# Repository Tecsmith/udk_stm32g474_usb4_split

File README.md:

# UDK Module - STM32F474 *(with 4-Port hub)*

**Keyboard MCU**

- *Refer to https://github.com/tecsmith/udk for information on the **Universal Design Keyboards** (UDK) - MCU Modules*

# Featuring

- `STM32G474`
- `CH334` (3-ports exposed as USB-A receptacles)

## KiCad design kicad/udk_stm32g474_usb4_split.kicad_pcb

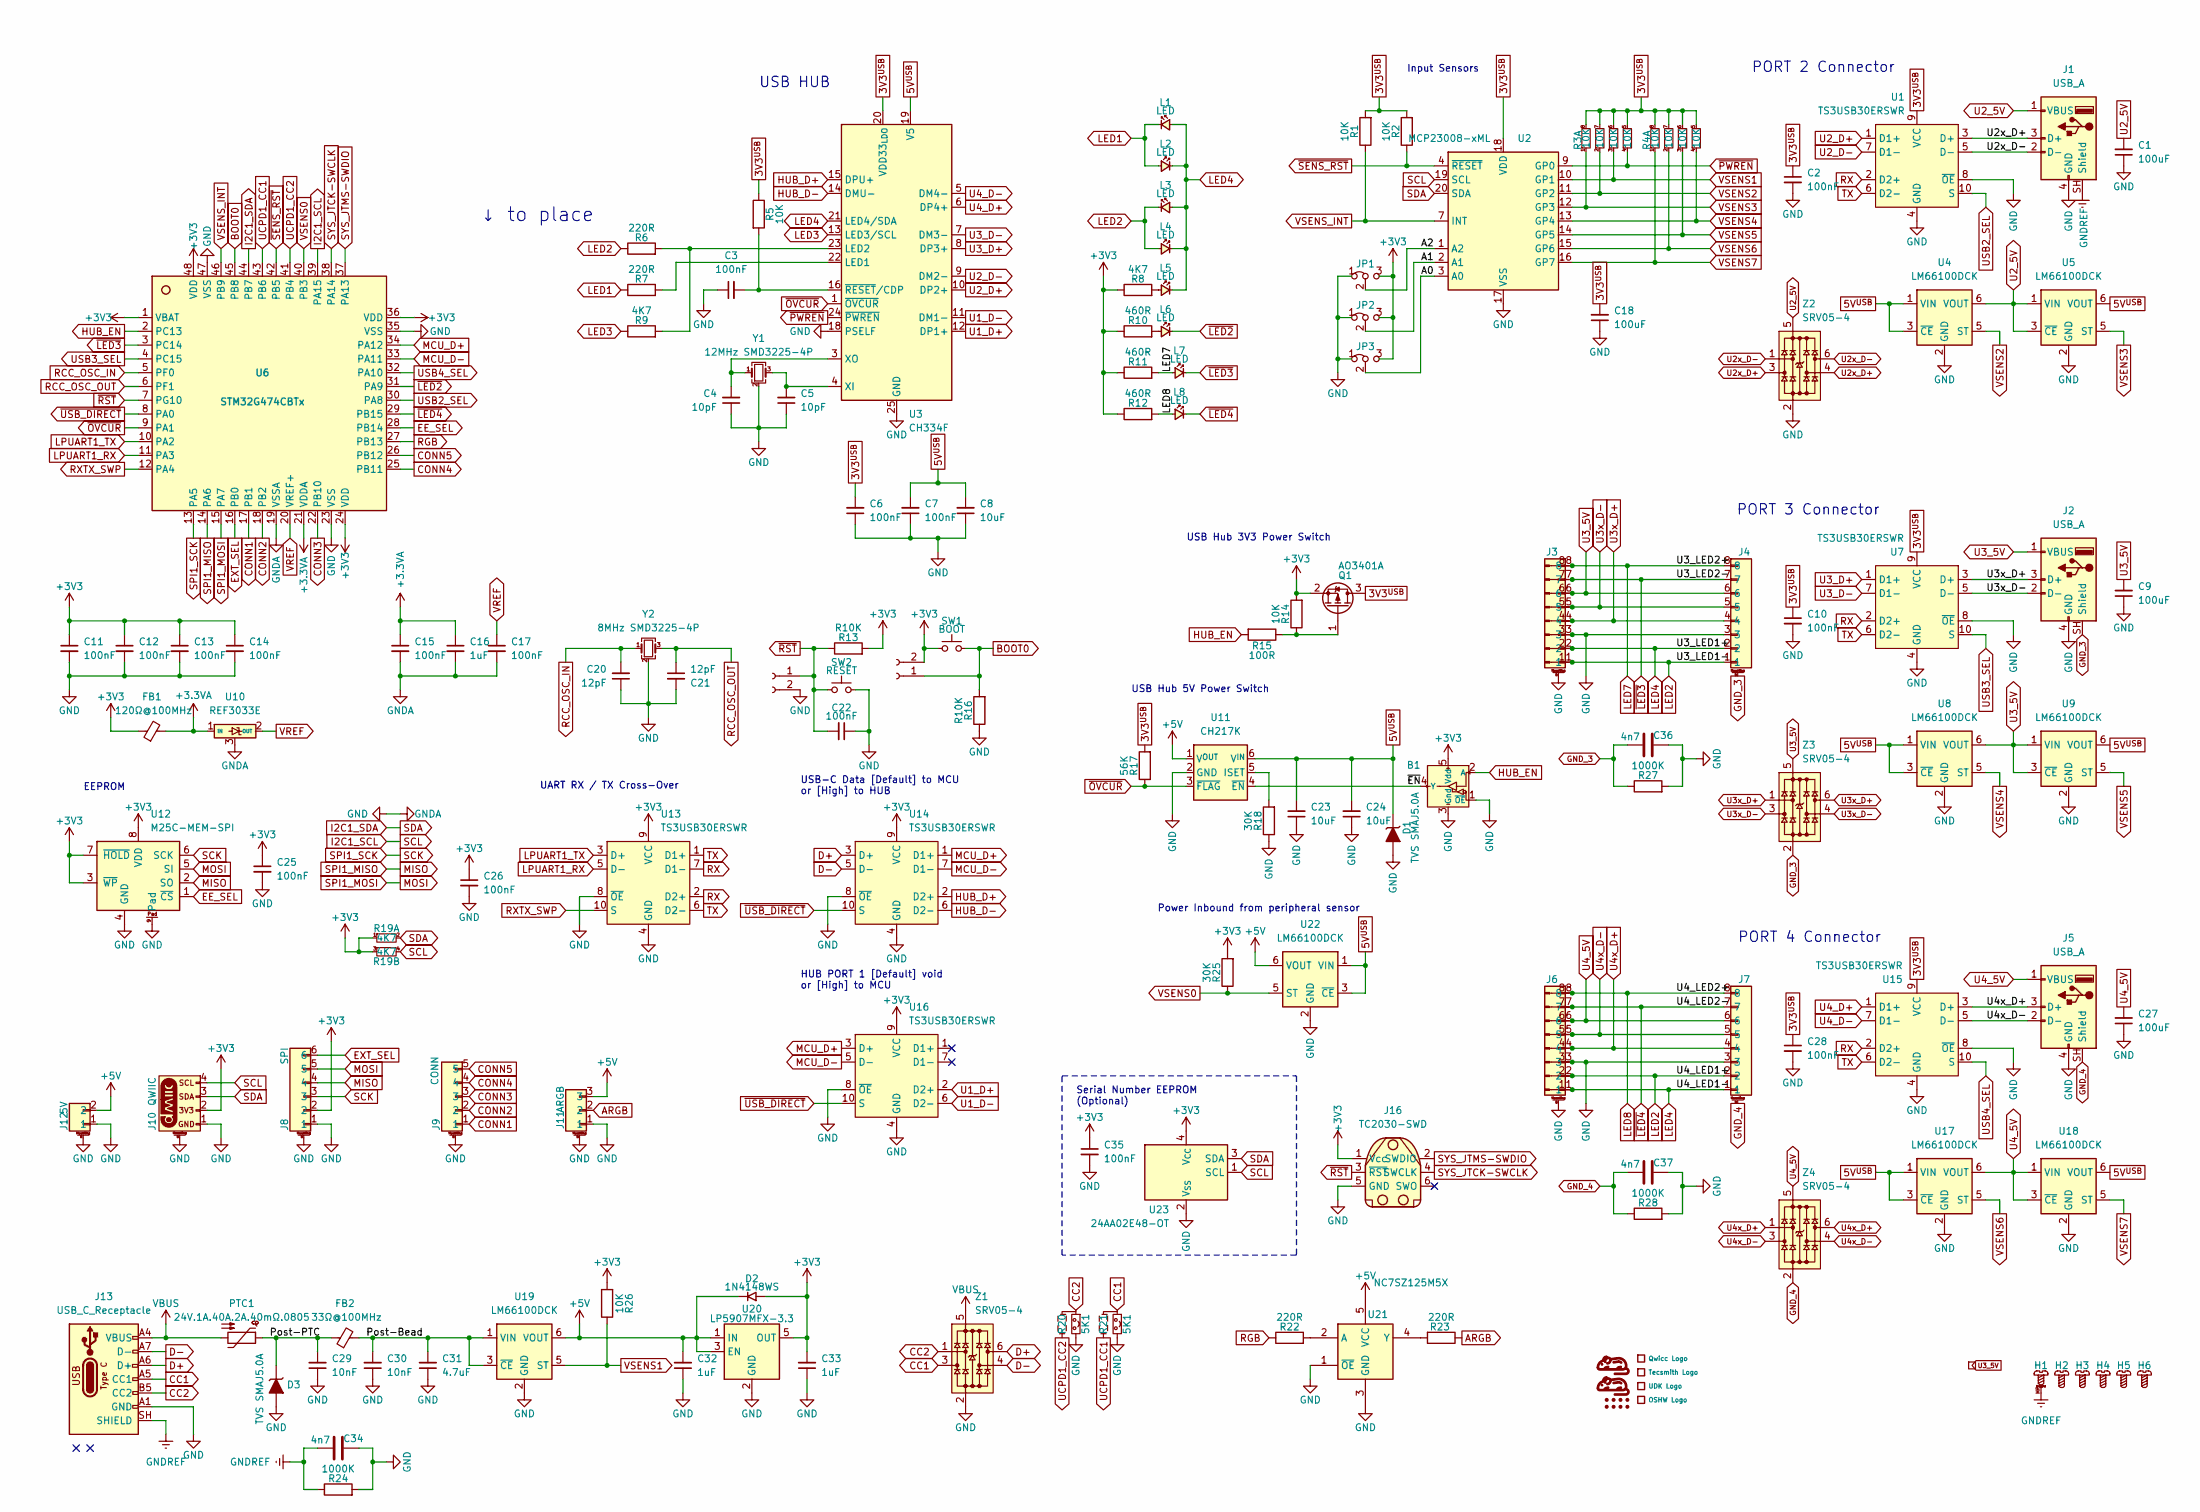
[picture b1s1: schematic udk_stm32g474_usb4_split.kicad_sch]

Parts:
B1: SOT-23-5
B2, B3: mouse-bite-2mm-slot
C1, C9, C27: 100uF; C_0603_1608Metric
C2, C3, C6, C10, C11, C12, C13, C14, C15, C17, C22, C25, C26, C28, C35: 100nF; C_0402_1005Metric
C4, C5: 10pF; C_0402_1005Metric
C7: 100nF; C_0603_1608Metric
C8, C23, C24: 10uF; C_0603_1608Metric
C16: 1uF; C_0402_1005Metric
C18: 100uF; C_0402_1005Metric
C20, C21: 12pF; C_0402_1005Metric
C29, C30: 10nF; C_0603_1608Metric
C31: 4.7uF; C_0603_1608Metric
C32, C33: 1uF; C_0603_1608Metric
C34, C36, C37: 4n7; C_0805_2012Metric_Pad1.18x1.45mm_HandSolder
D1, D3: TVS SMAJ5.0A; D_SMA
D2: 1N4148WS; D_SOD-323_HandSoldering
FB1: 120Ω@100MHz; L_0603_1608Metric; LCSC C88984
FB2: 33Ω@100MHz; L_0603_1608Metric; LCSC C88984
H1: Mount_M2_Rel
H2, H3, H4, H5, H6: Hole_M2
J1, J2, J5: USB_A; USB_A_Molex_67643_Horizontal
J3, J4, J6, J7: JST_SH_SM08B-SRSS-TB_1x08-1MP_P1.00mm_Horizontal
J8: SPI; JST_SH_SM06B-SRSS-TB_1x06-1MP_P1.00mm_Horizontal
J9: CONN; JST_SH_SM05B-SRSS-TB_1x05-1MP_P1.00mm_Horizontal
J10: QWIIC; JST_SH_SM04B-SRSS-TB_1x04-1MP_P1.00mm_Horizontal
J11: ARGB; JST_SH_SM03B-SRSS-TB_1x03-1MP_P1.00mm_Horizontal
J12: 5V; JST_SH_SM02B-SRSS-TB_1x02-1MP_P1.00mm_Horizontal
J13: USB_C_Receptacle; USB_C_Receptacle_GCT_USB4105-xx-A_16P_TopMnt_Horizontal
J14, J15: Conn_01x08_Pin; mouse-bite-2mm-weave
J16: TC2030-SWD; Tag-Connect_TC2030-IDC-NL_2x03_P1.27mm_Vertical
J17, J18: Conn_01x02_Socket; PinSocket_1x02_P2.54mm_Vertical
JP1, JP2, JP3: Jumper_3_Bridged12; SolderJumper-3_P1.3mm_Bridged12_RoundedPad1.0x1.5mm
L1, L2, L3, L4, L5, L6, L7, L8: LED; LED_0603_1608Metric
PTC1: 24V.1A.40A.2A.40mΩ.0805; L_0805_2012Metric; LCSC C42369218
Q1: AO3401A; SOT-23
R1, R2, R5, R14, R26: 10K; R_0402_1005Metric
R3, R4: 10K; R_Array_Convex_4x0402
R6, R7: 220R; R_0402_1005Metric
R8, R9: 4K7; R_0402_1005Metric
R10, R11, R12: 460R; R_0402_1005Metric
R13, R16: R10K; R_0402_1005Metric
R15: 100R; R_0402_1005Metric
R17: 56K; R_0402_1005Metric
R18, R25: 30K; R_0402_1005Metric
R19: 4K7; R_0603_1608_2up
R20: 5K1; Jumper_R_0603_M
R21: 5K1; Jumper_R_0603
R22, R23: 220R; R_0603_1608Metric
R24, R27, R28: 1000K; R_0805_2012Metric
SW1: BOOT; SW_Push_SPST_NO_Alps_SKRK
SW2: RESET; SW_Push_SPST_NO_Alps_SKRK
U1, U7, U13, U14, U15, U16: TS3USB30ERSWR; UQFN-10_1.4x1.8mm_P0.4mm
U2: MCP23008-xML; QFN-20-1EP_4x4mm_P0.5mm_EP2.7x2.7mm
U3: CH334F; QFN-24-1EP_4x4mm_P0.5mm_EP2.7x2.7mm_ThermalVias
U4, U5, U8, U9, U17, U18, U19, U22: LM66100DCK; SOT-363_SC-70-6
U6: STM32G474CBTx; LQFP-48_7x7mm_P0.5mm
U10: REF3033E; SOT-23-3
U11: CH217K; SOT23-6
U12: M25C-MEM-SPI; SOIC-8
U20: LP5907MFX-3.3; SOT-23-5
U21: NC7SZ125M5X; SOT-23-5
U23: 24AA02E48-OT; SOT-23-5
X1: Qwicc Logo; qwiic_5mm
X2: Tecsmith Logo; Tecsmith_20mm
X3: UDK Logo; UDK_5mm
X4: OSHW Logo; OSHW-Logo_5.7x6mm_SilkScreen
Y1: 12MHz SMD3225-4P; Crystal_SMD_3225-4Pin_3.2x2.5mm
Y2: 8MHz SMD3225-4P; Crystal_SMD_3225-4Pin_3.2x2.5mm
Z1, Z2, Z3, Z4: SRV05-4; TSOP-6_1.65x3.05mm_P0.95mm
j19: NetJunction_T_0.508_0.254_0.508mm
p1, p2, p3, p4, p5, p6, p7, p8: mouse-bite-2mm-slot-short

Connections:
3V3^{USB}: C2.1, C6.2, C10.1, C18.2, C28.1, Q1.3 (D), R1.2, R2.2, R3.5, R3.6, R3.7, R3.8, R4.5, R4.6, R4.7, R4.8, R5.1, R17.2, U1.9 (VCC), U2.18 (VDD), U3.20 (VDD33_{LDO}), U7.9 (VCC), U15.9 (VCC)
5V^{USB}: C7.2, C8.2, C23.2, C24.2, D1.2 (A2), U3.19 (V5), U4.1 (VIN), U4.3 (~CE), U5.6 (VOUT), U8.1 (VIN), U8.3 (~CE), U9.6 (VOUT), U11.6 (V^{IN}), U17.1 (VIN), U17.3 (~CE), U18.6 (VOUT), U22.1 (VIN), U22.3 (~CE)
+3.3VA: C15.1, C16.1, FB1.2, U6.21 (VDDA), U10.1 (IN)
+3V3: B1.5 (Vdd), C11.1, C12.1, C13.1, C14.1, C25.1, C26.1, C33.2, C35.1, D2.2 (A), FB1.1, J8.2, J10.2, J16.1 (Vcc), J18.2, JP1.3 (B), JP2.3 (B), JP3.3 (B), Q1.2 (S), R8.1, R10.1, R11.1, R12.1, R13.2, R14.2, R19.1, R19.3, R25.2, R26.2, SW1.1, U6.1 (VBAT), U6.24 (VDD), U6.36 (VDD), U6.48 (VDD), U12.3 (~WP), U12.7 (~HOLD), U12.8 (VDD), U13.9 (VCC), U14.9 (VCC), U16.9 (VCC), U20.5 (OUT), U23.4 (V_{CC})
+5V: C32.2, D2.1 (K), J11.3, J12.2, U11.1 (V^{OUT}), U19.6 (VOUT), U20.1 (IN), U20.3 (EN), U21.5 (VCC), U22.6 (VOUT)
/A0: JP3.2 (C), U2.3 (A0)
/A1: JP2.2 (C), U2.2 (A1)
/A2: JP1.2 (C), U2.1 (A2)
/Post-Bead: C30.2, C31.2, FB2.2, U19.1 (VIN), U19.3 (~CE)
/Post-PTC: C29.2, D3.2 (A2), FB2.1, PTC1.1
/~EN: B1.4 (Y), U11.4 (~EN)
ARGB: J11.2, R23.1
BOOT0: J18.1, R16.2, SW1.2, U6.45 (PB8)
CC1: J13.A5 (CC1), R21.1, Z1.3
CC2: J13.B5 (CC2), R20.1, Z1.1
CONN1: J9.1, U6.17 (PB1)
CONN2: J9.2, U6.18 (PB2)
CONN3: J9.3, U6.22 (PB10)
CONN4: J9.4, U6.25 (PB11)
CONN5: J9.5, U6.26 (PB12)
D+: J13.A6 (D+), J13.B6 (D+), U14.3 (D+), Z1.6
D-: J13.A7 (D-), J13.B7 (D-), U14.5 (D-), Z1.4
EE_SEL: U6.28 (PB14), U12.1 (~CS)
EXT_SEL: J8.6, U6.16 (PB0)
GND: B1.1 (~OE), B1.3 (Gnd), C1.1, C2.2, C3.1, C4.1, C5.1, C6.1, C7.1, C8.1, C9.1, C10.2, C11.2, C12.2, C13.2, C14.2, C15.2, C16.2, C17.2, C18.1, C20.1, C21.2, C22.1, C23.1, C24.1, C25.2, C26.2, C27.1, C28.2, C29.1, C30.1, C31.1, C32.1, C33.1, C34.2, C35.2, C36.2, C37.2, D1.1 (A1), D3.1 (A1), J1.4 (GND), J2.4 (GND), J3.3, J3.MP, J4.3, J5.4 (GND), J6.3, J6.MP, J7.3, J8.1, J8.MP, J9.MP, J10.1, J10.MP, J11.1, J11.MP, J12.1, J12.MP, J13.A1 (GND), J13.A12 (GND), J13.B1 (GND), J13.B12 (GND), J14.3, J15.3, J16.5 (GND), J17.2, JP1.1 (A), JP2.1 (A), JP3.1 (A), R16.1, R18.1, R20.2, R21.2, R24.2, R27.2, R28.2, SW2.2, U1.4 (GND), U1.8 (~OE), U2.17 (VSS), U3.18 (PSELF), U3.25 (GND), U4.2 (GND), U5.2 (GND), U6.19 (VSSA), U6.23 (VSS), U6.35 (VSS), U6.47 (VSS), U7.4 (GND), U7.8 (~OE), U8.2 (GND), U9.2 (GND), U10.3 (GND), U11.2 (GND), U12.4 (GND), U12.9 (Pad), U13.4 (GND), U13.8 (~OE), U14.4 (GND), U14.8 (~OE), U15.4 (GND), U15.8 (~OE), U16.4 (GND), U16.8 (~OE), U17.2 (GND), U18.2 (GND), U19.2 (GND), U20.2 (GND), U21.1 (~OE), U21.3 (GND), U22.2 (GND), U23.2 (V_{SS}), Y1.2 (G), Y1.4 (G), Y2.2 (G), Y2.4 (G), Z1.2, Z2.2
GNDREF: C34.1, H1.MP, J1.SH (Shield), J13.SH (SHIELD), R24.1
GND_3: C36.1, J2.SH (Shield), J4.MP, R27.1, Z3.2
GND_4: C37.1, J5.SH (Shield), J7.MP, R28.1, Z4.2
HUB_D+: U3.15 (DPU+), U14.2 (D2+)
HUB_D-: U3.14 (DMU-), U14.6 (D2-)
HUB_EN: B1.2 (A), R15.2, U6.2 (PC13)
I2C1_SCL: J10.4, R19.4, U2.19 (SCL), U6.39 (PA15), U23.1 (SCL)
I2C1_SDA: J10.3, R19.2, U2.20 (SDA), U6.44 (PB7), U23.3 (SDA)
LED1: L1.1 (K), L2.2 (A), R7.1
LED2: J3.1, J4.1, J6.2, J7.2, J14.1, J15.2, L3.1 (K), L4.2 (A), R6.1
LED3: R9.1, U3.13 (LED3/SCL)
LED4: J3.2, J4.2, J6.1, J7.1, J14.2, J15.1, L1.2 (A), L2.1 (K), L3.2 (A), L4.1 (K), L5.1 (K), U3.21 (LED4/SDA)
LED7: J3.8, J4.8, J14.8, L7.2 (A), R11.2
LED8: J6.8, J7.8, J15.8, L8.2 (A), R12.2
LPUART1_RX: U6.11 (PA3), U13.5 (D-)
LPUART1_TX: U6.10 (PA2), U13.3 (D+)
MCU_D+: U6.34 (PA12), U14.1 (D1+), U16.3 (D+)
MCU_D-: U6.33 (PA11), U14.7 (D1-), U16.5 (D-)
MISO: J8.4, U6.14 (PA6), U12.2 (SO)
MOSI: J8.5, U6.15 (PA7), U12.5 (SI)
unnamed: L5.2 (A), R8.2
unnamed: L6.2 (A), R10.2
unnamed: Q1.1 (G), R14.1, R15.1
unnamed: R7.2, U3.22 (LED1)
unnamed: R6.2, R9.2, U3.23 (LED2)
unnamed: C5.2, U3.4 (XI), Y1.3
unnamed: C4.2, U3.3 (XO), Y1.1
unnamed: C3.2, R5.2, U3.16 (~RESET/CDP)
unnamed: R18.2, U11.5 (ISET)
unnamed: R22.2, U21.2 (A)
unnamed: R23.2, U21.4 (Y)
RCC_OSC_IN: C20.2, U6.5 (PF0), Y2.1
RCC_OSC_OUT: C21.1, U6.6 (PF1), Y2.3
RGB: R22.1, U6.27 (PB13)
RX: U1.2 (D2+), U7.2 (D2+), U13.2 (D2+), U13.7 (D1-), U15.2 (D2+)
RXTX_SWP: U6.12 (PA4), U13.10 (S)
SCK: J8.3, U6.13 (PA5), U12.6 (SCK)
SYS_JTCK-SWCLK: J16.4 (SWCLK), U6.38 (PA14)
SYS_JTMS-SWDIO: J16.2 (SWDIO), U6.37 (PA13)
TX: U1.6 (D2-), U7.6 (D2-), U13.1 (D1+), U13.6 (D2-), U15.6 (D2-)
U1_D+: U3.12 (DP1+), U16.2 (D2+)
U1_D-: U3.11 (DM1-), U16.6 (D2-)
U2_5V: C1.2, J1.1 (VBUS), U4.6 (VOUT), U5.1 (VIN), U5.3 (~CE), Z2.5
U2_D+: U1.1 (D1+), U3.10 (DP2+)
U2_D-: U1.7 (D1-), U3.9 (DM2-)
U2x_D+: J1.3 (D+), U1.3 (D+), Z2.3, Z2.4
U2x_D-: J1.2 (D-), U1.5 (D-), Z2.1, Z2.6
U3_5V: C9.2, J2.1 (VBUS), J3.6, J4.6, J14.6, U8.6 (VOUT), U9.1 (VIN), U9.3 (~CE), Z3.5, j19.1
U3_D+: U3.8 (DP3+), U7.1 (D1+)
U3_D-: U3.7 (DM3-), U7.7 (D1-)
U3x_D+: J2.3 (D+), J3.4, J4.4, J14.4, U7.3 (D+), Z3.1, Z3.6
U3x_D-: J2.2 (D-), J3.5, J4.5, J14.5, U7.5 (D-), Z3.3, Z3.4
U4_5V: C27.2, J5.1 (VBUS), J6.6, J7.6, J15.6, U17.6 (VOUT), U18.1 (VIN), U18.3 (~CE), Z4.5
U4_D+: U3.6 (DP4+), U15.1 (D1+)
U4_D-: U3.5 (DM4-), U15.7 (D1-)
U4x_D+: J5.3 (D+), J6.4, J7.4, J15.4, U15.3 (D+), Z4.1, Z4.6
U4x_D-: J5.2 (D-), J6.5, J7.5, J15.5, U15.5 (D-), Z4.3, Z4.4
UCPD1_CC1: R21.3, U6.43 (PB6)
UCPD1_CC2: R20.3, U6.41 (PB4)
USB2_SEL: U1.10 (S), U6.30 (PA8)
USB3_SEL: U6.4 (PC15), U7.10 (S)
USB4_SEL: U6.32 (PA10), U15.10 (S)
VBUS: J13.A4 (VBUS), J13.A9 (VBUS), J13.B4 (VBUS), J13.B9 (VBUS), PTC1.2, Z1.5
VREF: C17.1, U6.20 (VREF+), U10.2 (OUT)
VSENS0: R25.1, U6.40 (PB3), U22.5 (ST)
VSENS1: R3.3, R26.1, U2.10 (GP1), U19.5 (ST)
VSENS2: R3.2, U2.11 (GP2), U4.5 (ST)
VSENS3: R3.1, U2.12 (GP3), U5.5 (ST)
VSENS4: R4.4, U2.13 (GP4), U8.5 (ST)
VSENS5: R4.3, U2.14 (GP5), U9.5 (ST)
VSENS6: R4.2, U2.15 (GP6), U17.5 (ST)
VSENS7: R4.1, U2.16 (GP7), U18.5 (ST)
VSENS_INT: R1.1, U2.7 (INT), U6.46 (PB9)
~LED2: L6.1 (K), U6.31 (PA9)
~LED3: J3.7, J4.7, J14.7, L7.1 (K), U6.3 (PC14)
~LED4: J6.7, J7.7, J15.7, L8.1 (K), U6.29 (PB15)
~OVCUR: R17.1, U3.1 (~OVCUR), U6.9 (PA1), U11.3 (~FLAG)
~PWREN: R3.4, U2.9 (GP0), U3.24 (~PWREN)
~RST: C22.2, J16.3 (~RST), J17.1, R13.1, SW2.1, U6.7 (PG10)
~SENS_RST: R2.1, U2.4 (~RESET), U6.42 (PB5)
~USB_DIRECT: U6.8 (PA0), U14.10 (S), U16.10 (S)

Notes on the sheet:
PORT 3 Connector
USB Hub 3V3 Power Switch
UART RX / TX Cross-Over
PORT 2 Connector
↓ to place
Input Sensors
HUB PORT 1 [Default] void or [High] to MCU
Power Inbound from peripheral sensor
USB Hub 5V Power Switch
USB HUB
PORT 4 Connector
USB-C Data [Default] to MCU or [High] to HUB
Serial Number EEPROM (Optional)
EEPROM

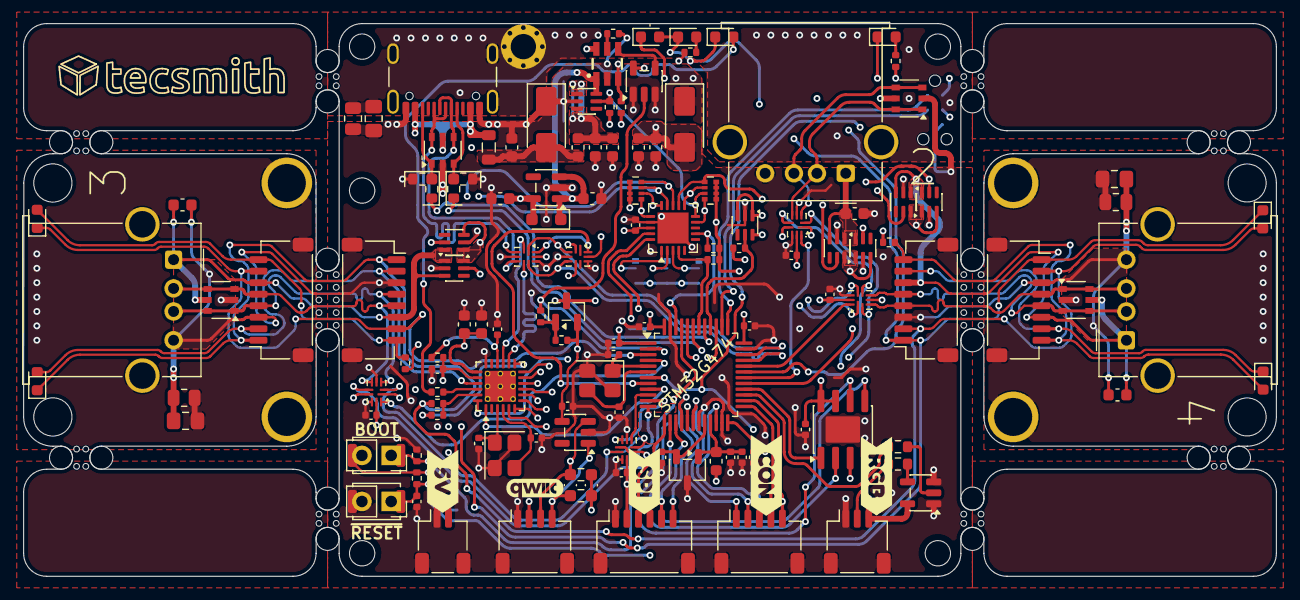
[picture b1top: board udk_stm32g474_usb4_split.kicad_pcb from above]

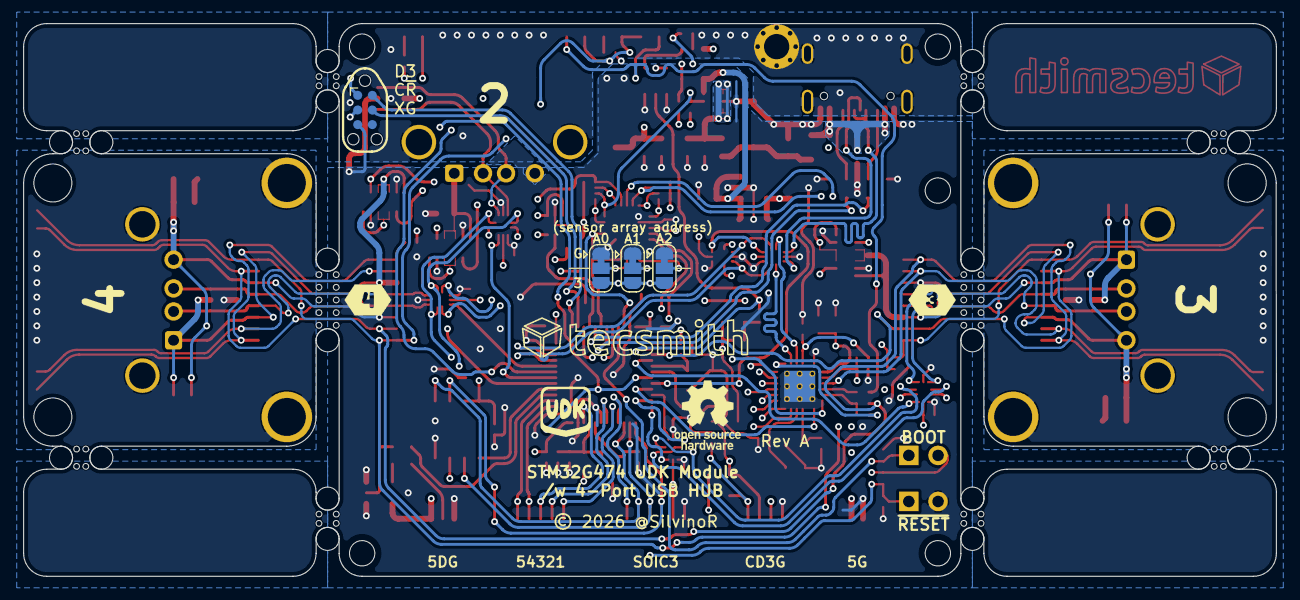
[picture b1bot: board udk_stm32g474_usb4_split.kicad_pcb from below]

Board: 4 copper layers, 108.8 x 48.0 mm, 159 parts (10 on the bottom side), 106 nets.

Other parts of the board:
kibuzzard-6A423E00: G***; kibuzzard-6A423E00
kibuzzard-6A423E1B: G***; kibuzzard-6A423E1B
kibuzzard-6A423E36: G***; kibuzzard-6A423E36
kibuzzard-6A423EE6: G***; kibuzzard-6A423EE6
kibuzzard-6A424CF7: G***; kibuzzard-6A424CF7
kibuzzard-6A424D38: G***; kibuzzard-6A424D38

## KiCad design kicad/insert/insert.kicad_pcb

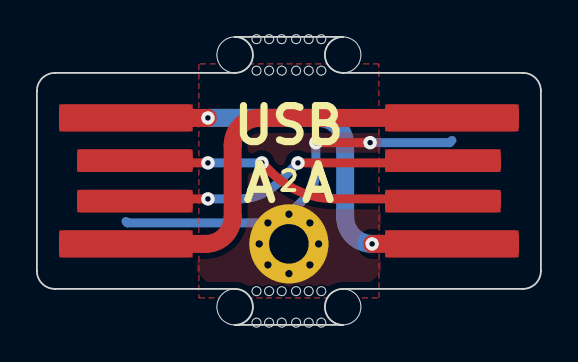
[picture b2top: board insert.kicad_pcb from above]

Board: 2 copper layers, 28.0 x 16.0 mm, 5 parts (0 on the bottom side), 5 nets.

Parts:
J1, J2: USB_A; USB_A_PCB
TP1: MountingHole_2.2mm_M2_Pad_Via
mouse-bite-2mm-slot, mouse-bite-2mm-slot#2: VAL**; mouse-bite-2mm-slot

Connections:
/D+: J1.3 (D+), J2.3 (D+)
/D-: J1.2 (D-), J2.2 (D-)
/GND: J1.4 (GND), J2.4 (GND)
/VBUS: J1.1 (VBUS), J2.1 (VBUS)
GROUND: J1.SH (Shield), J2.SH (Shield), TP1.1

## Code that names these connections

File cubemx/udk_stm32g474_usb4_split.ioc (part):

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Mcu.Name=STM32G474C(B-C-E)Tx
Mcu.Package=LQFP48
Mcu.UserName=STM32G474CBTx
PA11.Mode=Device
PA11.Signal=USB_DM
PA12.Mode=Device
PA12.Signal=USB_DP
PA13.Mode=Serial_Wire
PA13.Signal=SYS_JTMS-SWDIO
PA14.Mode=Serial_Wire
PA14.Signal=SYS_JTCK-SWCLK
PA15.Mode=I2C
PA15.Signal=I2C1_SCL
PA2.Mode=Asynchronous
PA2.Signal=LPUART1_TX
PA3.Mode=Asynchronous
PA3.Signal=LPUART1_RX
PA5.Mode=Full_Duplex_Master
PA5.Signal=SPI1_SCK
PA6.Mode=Full_Duplex_Master
PA6.Signal=SPI1_MISO
PA7.Mode=Full_Duplex_Master
PA7.Signal=SPI1_MOSI
PB4.Mode=Sink_AllSignals
PB4.Signal=UCPD1_CC2
PB6.Mode=Sink_AllSignals
PB6.Signal=UCPD1_CC1
PB7.Mode=I2C
PB7.Signal=I2C1_SDA
PF0-OSC_IN.Mode=HSE-External-Oscillator
PF0-OSC_IN.Signal=RCC_OSC_IN
PF1-OSC_OUT.Mode=HSE-External-Oscillator
PF1-OSC_OUT.Signal=RCC_OSC_OUT
RCC.HSE_VALUE=8000000
RCC.SYSCLKFreq_VALUE=16000000
board=custom

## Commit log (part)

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2026-06-29 upload
2026-06-29 added `24AA02E48`

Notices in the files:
kicad/udk_stm32g474_usb4_split.kicad_pcb:
© 2026 @SilvinoR
